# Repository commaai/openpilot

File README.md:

<div align="center" style="text-align: center;">

<h1>openpilot</h1>

<p>
  <b>openpilot is an operating system for robotics.</b>
  <br>
  Currently, it upgrades the driver assistance system in 300+ supported cars.
</p>

<h3>
  <a href="https://docs.comma.ai">Docs</a>
  <span> · </span>
  <a href="https://docs.comma.ai/contributing/roadmap/">Roadmap</a>
  <span> · </span>
  <a href="https://github.com/commaai/openpilot/blob/master/docs/CONTRIBUTING.md">Contribute</a>
  <span> · </span>
  <a href="https://discord.comma.ai">Community</a>
  <span> · </span>
  <a href="https://comma.ai/shop">Try it on a comma four</a>
</h3>

Quick start: `bash <(curl -fsSL openpilot.comma.ai)`

</div>

<table>
  <tr>
    <td></td>
    <td></td>
    <td></td>
  </tr>
</table>

Using openpilot in a car
------

To use openpilot in a car, you need four things:
1. **Supported Device:** a comma four, available at [comma.ai/shop/comma-four](https://www.comma.ai/shop/comma-four).
2. **Software:** The setup procedure for the comma four allows users to enter a URL for custom software. Use the URL `openpilot.comma.ai` to install the release version.
3. **Supported Car:** Ensure that you have one of [the 300+ supported cars](docs/CARS.md).
4. **Car Harness:** You will also need a [car harness](https://comma.ai/shop/car-harness) to connect your comma four to your car.

We have detailed instructions for [how to install the harness and device in a car](https://comma.ai/setup). Note that it's possible to run openpilot on [other hardware](https://blog.comma.ai/self-driving-car-for-free/), although it's not plug-and-play.

### Branches

Running `master` and other branches directly is supported, but it's recommended to run one of the following prebuilt branches:

| comma four branch      | comma 3X branch        | URL                                    | description                                                                         |
|------------------------|------------------------|----------------------------------------|-------------------------------------------------------------------------------------|
| `release-mici`         | `release-tizi`         | openpilot.comma.ai                     | This is openpilot's release branch.                                                 |
| `release-mici-staging` | `release-tizi-staging` | openpilot-test.comma.ai                | This is the staging branch for releases. Use it to get new releases slightly early. |
| `nightly`              | `nightly`              | openpilot-nightly.comma.ai             | This is the bleeding edge development branch. Do not expect this to be stable.      |
| `nightly-dev`          | `nightly-dev`          | installer.comma.ai/commaai/nightly-dev | Same as nightly, but includes experimental development features for some cars.      |

For [chestnut](https://comma.ai/shop/chestnut), use the following installer URLs:

| branch                       | URL                                                        | description                                                                         |
|------------------------------|------------------------------------------------------------|-------------------------------------------------------------------------------------|
| `nightly-chestnut`           | installer.comma.ai/commaai/nightly-chestnut                | This is the bleeding edge development branch. Do not expect this to be stable.      |
| `nightly-chestnut-dev`       | installer.comma.ai/commaai/nightly-chestnut-dev            | Same as nightly, but includes experimental development features for some cars.      |

To start developing openpilot
------

openpilot is developed by [comma](https://comma.ai/) and by users like you. We welcome both pull requests and issues on [GitHub](http://github.com/commaai/openpilot).

* Join the [community Discord](https://discord.comma.ai)
* Check out [the contributing docs](docs/CONTRIBUTING.md)
* Check out the [openpilot tools](openpilot/tools/)
* Code documentation lives at https://docs.comma.ai
* Information about running openpilot lives on the [community wiki](https://github.com/commaai/openpilot/wiki)

Want to get paid to work on openpilot? [comma is hiring](https://comma.ai/jobs#open-positions) and offers lots of [bounties](https://comma.ai/bounties) for external contributors.

Safety and Testing
----

* openpilot observes [ISO26262](https://en.wikipedia.org/wiki/ISO_26262) guidelines, see [SAFETY.md](docs/SAFETY.md) for more details.
* openpilot has software-in-the-loop [tests](.github/workflows/tests.yaml) that run on every commit.
* The code enforcing the safety model lives in panda and is written in C, see [code rigor](https://github.com/commaai/panda#code-rigor) for more details.
* panda has software-in-the-loop [safety tests](https://github.com/commaai/panda/tree/master/tests/safety).
* Internally, we have a hardware-in-the-loop Jenkins test suite that builds and unit tests the various processes.
* panda has additional hardware-in-the-loop [tests](https://github.com/commaai/panda/blob/master/Jenkinsfile).
* We run the latest openpilot in a testing closet containing 10 comma devices continuously replaying routes.

<details>
<summary>MIT Licensed</summary>

openpilot is released under the MIT license. Some parts of the software are released under other licenses as specified.

Any user of this software shall indemnify and hold harmless Comma.ai, Inc. and its directors, officers, employees, agents, stockholders, affiliates, subcontractors and customers from and against all allegations, claims, actions, suits, demands, damages, liabilities, obligations, losses, settlements, judgments, costs and expenses (including without limitation attorneys’ fees and costs) which arise out of, relate to or result from any use of this software by user.

**THIS IS ALPHA QUALITY SOFTWARE FOR RESEARCH PURPOSES ONLY. THIS IS NOT A PRODUCT.
YOU ARE RESPONSIBLE FOR COMPLYING WITH LOCAL LAWS AND REGULATIONS.
NO WARRANTY EXPRESSED OR IMPLIED.**
</details>

<details>
<summary>User Data and comma Account</summary>

By default, openpilot uploads driving data to our servers. You can also access your data through [comma connect](https://connect.comma.ai/). We use your data to train better models and improve openpilot for everyone.

openpilot is open source software, and users can disable data collection if they wish.

openpilot logs the road-facing cameras, CAN, GPS, IMU, magnetometer, thermal sensors, crashes, and operating system logs.
The driver-facing camera and microphone are only logged if you explicitly opt-in in settings.

By using openpilot, you agree to [our Privacy Policy](https://comma.ai/privacy). You understand that use of this software or its related services will generate certain types of user data, which may be logged and stored at the sole discretion of comma. By accepting this agreement, you grant an irrevocable, perpetual, worldwide right to comma for the use of this data.
</details>

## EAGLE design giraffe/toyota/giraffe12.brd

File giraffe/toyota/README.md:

Toyota giraffe
====

Get your panda deeper into your compatible Toyota vehicle

The switches
====

The 4 DIP switches control signals to the stock ADAS system

- 1 -- ADAS CAN1 -> main body CAN

- 2 -- ADAS CAN1 -> panda CAN3 (OBDII pins 12 & 13)

- 3 -- IGNITION POWER -> panda power

- 4 -- ADAS power & ignition -> power & ignition

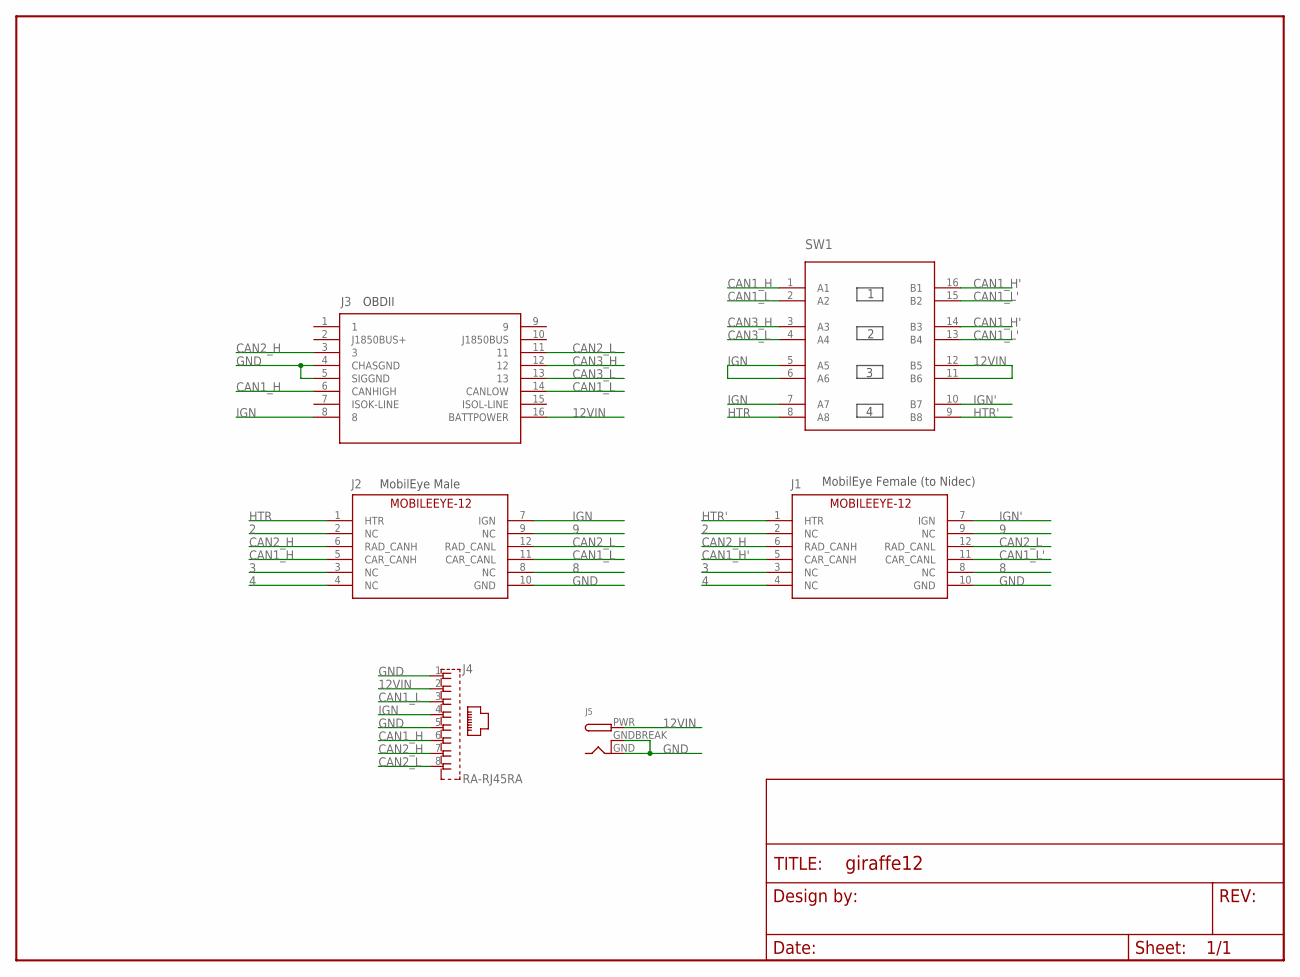
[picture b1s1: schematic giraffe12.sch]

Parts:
FRAME1: FRAME-LETTERNO_PACKAGE; DUMMY
J1: MOBILEEYE-12FEMALE; 2X6-TE-FEMALE
J2: MOBILEEYE-12MALE; 2X6-TE-RA
J3: OBDII-FEMALE-CUT; OBDII-FEMALE-MIDCUT
J4: RA-RJ45RA; RA-RJ45
J5: DCBARRELPTH; DCJACK_2MM_PTH
SW1: 4XDPSTSMT; 4-DPST

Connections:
2: J1.2 (NC), J2.2 (NC)
3: J1.3 (NC), J2.3 (NC)
4: J1.4 (NC), J2.4 (NC)
8: J1.8 (NC), J2.8 (NC)
9: J1.9 (NC), J2.9 (NC)
12VIN: J3.16 (BATTPOWER), J4.2, J5.PWR, SW1.11 (B6), SW1.12 (B5)
CAN1_H: J2.5 (CAR_CANH), J3.6 (CANHIGH), J4.6, SW1.1 (A1)
CAN1_H': J1.5 (CAR_CANH), SW1.14 (B3), SW1.16 (B1)
CAN1_L: J2.11 (CAR_CANL), J3.14 (CANLOW), J4.3, SW1.2 (A2)
CAN1_L': J1.11 (CAR_CANL), SW1.13 (B4), SW1.15 (B2)
CAN2_H: J1.6 (RAD_CANH), J2.6 (RAD_CANH), J3.3, J4.7
CAN2_L: J1.12 (RAD_CANL), J2.12 (RAD_CANL), J3.11, J4.8
CAN3_H: J3.12, SW1.3 (A3)
CAN3_L: J3.13, SW1.4 (A4)
GND: J1.10 (GND), J2.10 (GND), J3.4 (CHASGND), J3.5 (SIGGND), J4.1, J4.5, J5.GND, J5.GNDBREAK
HTR: J2.1 (HTR), SW1.8 (A8)
HTR': J1.1 (HTR), SW1.9 (B8)
IGN: J2.7 (IGN), J3.8, J4.4, SW1.5 (A5), SW1.6 (A6), SW1.7 (A7)
IGN': J1.7 (IGN), SW1.10 (B7)

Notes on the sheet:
OBDII
MobilEye Male
MobilEye Female (to Nidec)

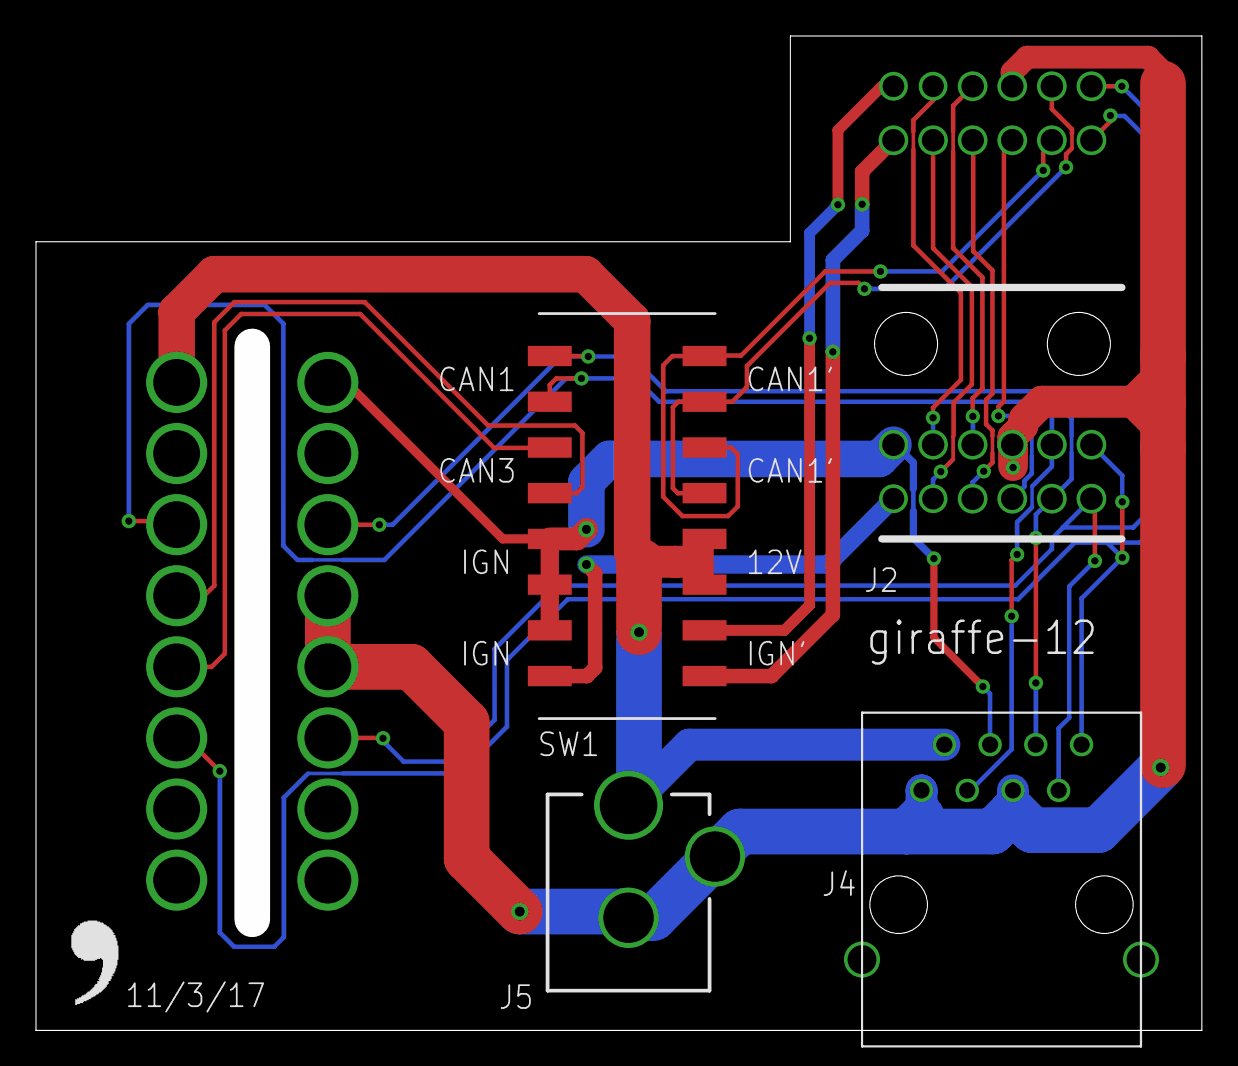
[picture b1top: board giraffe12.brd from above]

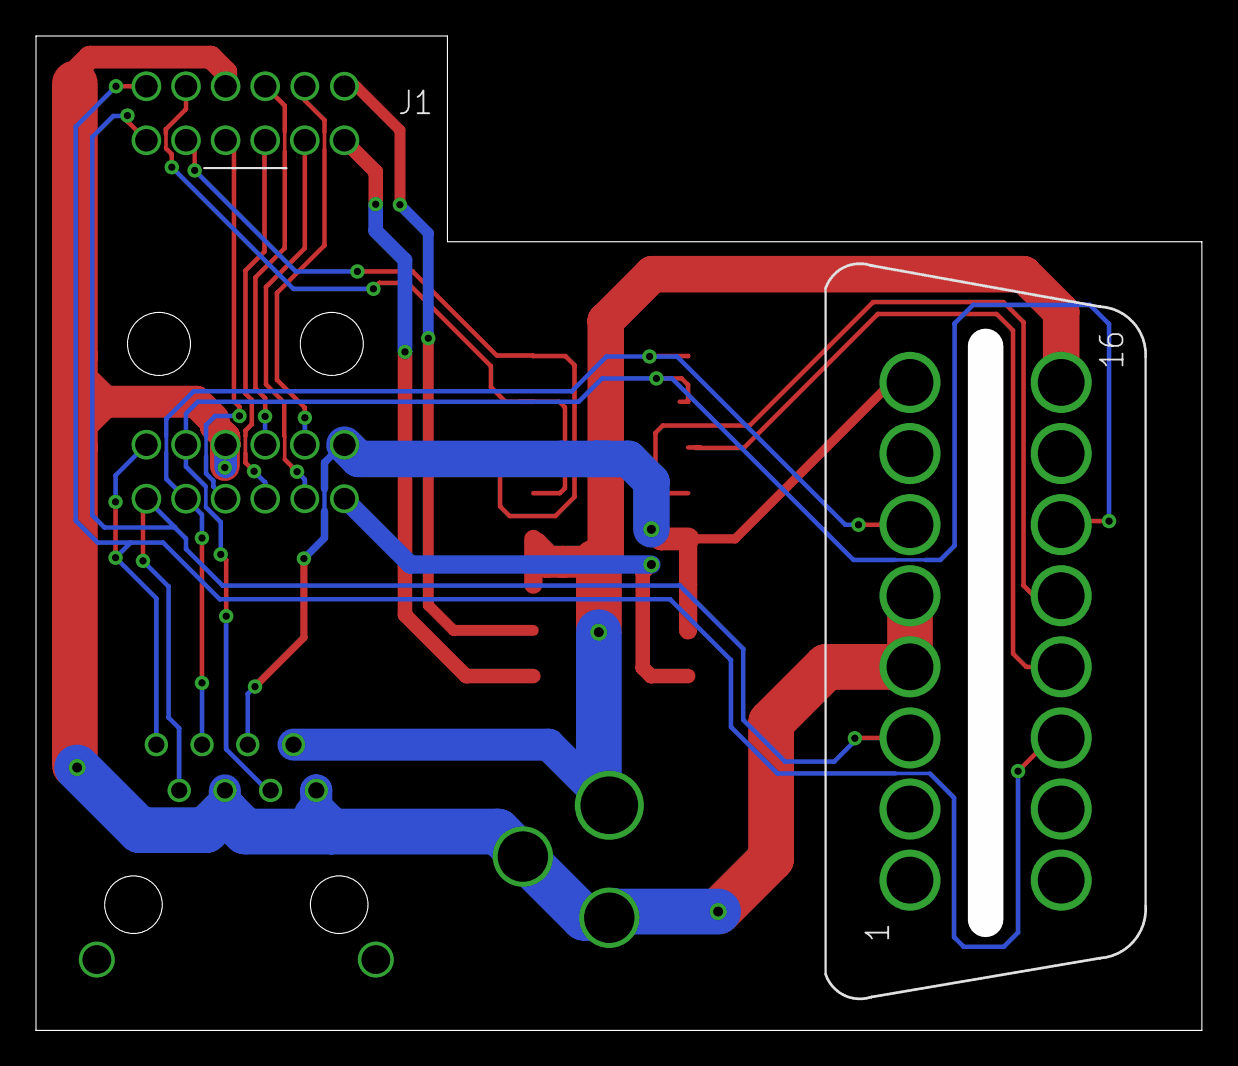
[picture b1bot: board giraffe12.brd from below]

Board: 2 copper layers, 64.8 x 55.2 mm, 8 parts (2 on the bottom side), 19 nets.

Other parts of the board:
U$1: LOGO

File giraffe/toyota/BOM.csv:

Ref Des,Package,Manufacturer PN,Qty,Link
J1,12-pin-RA,1318772-2,1,http://www.mouser.com/Search/ProductDetail.aspx?R=1318772-2v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
J2,12-pin,1318774-1,1,http://www.mouser.com/Search/ProductDetail.aspx?R=1318774-1v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
,,1123343-1,12,https://www.digikey.com/product-detail/en/te-connectivity-am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
,,PRPC040SAAN-RC,1,https://www.digikey.com/products/en?keywords=S1011EC-40-ND
J3,16-pin,OBDII-FEMALE,1,https://cn1514770021qfbj.en.alibaba.com/product/60598699808-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
J4,RJ45-RA,A-2004-2-4-LPS-N-R,1,https://www.digikey.com/product-detail/en/assmann-wsw-compon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
J5,3-pin,EJ508A,1,https://www.digikey.com/products/en?keywords=ej508a
SW1,SMD,204-214ST,1,https://www.digikey.com/scripts/DkSearch/dksus.dll?Detail&it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
SCREWs,Phillips,92010A118,2,https://www.mcmaster.com/#catalog/92010A118

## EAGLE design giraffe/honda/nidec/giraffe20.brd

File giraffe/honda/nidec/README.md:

Honda giraffe
====

Get your panda deeper into your Honda Civic or Acura ILX

The switches
====

The 4 DIP switches control signals to the stock ADAS system

- 1 -- ADAS CAN1 -> main body CAN

- 2 -- ADAS CAN1 -> panda CAN3 (OBDII pins 12 & 13)

- 3 -- ADAS CAN2 -> radar CAN

- 4 -- ADAS power & ignition -> power & ignition

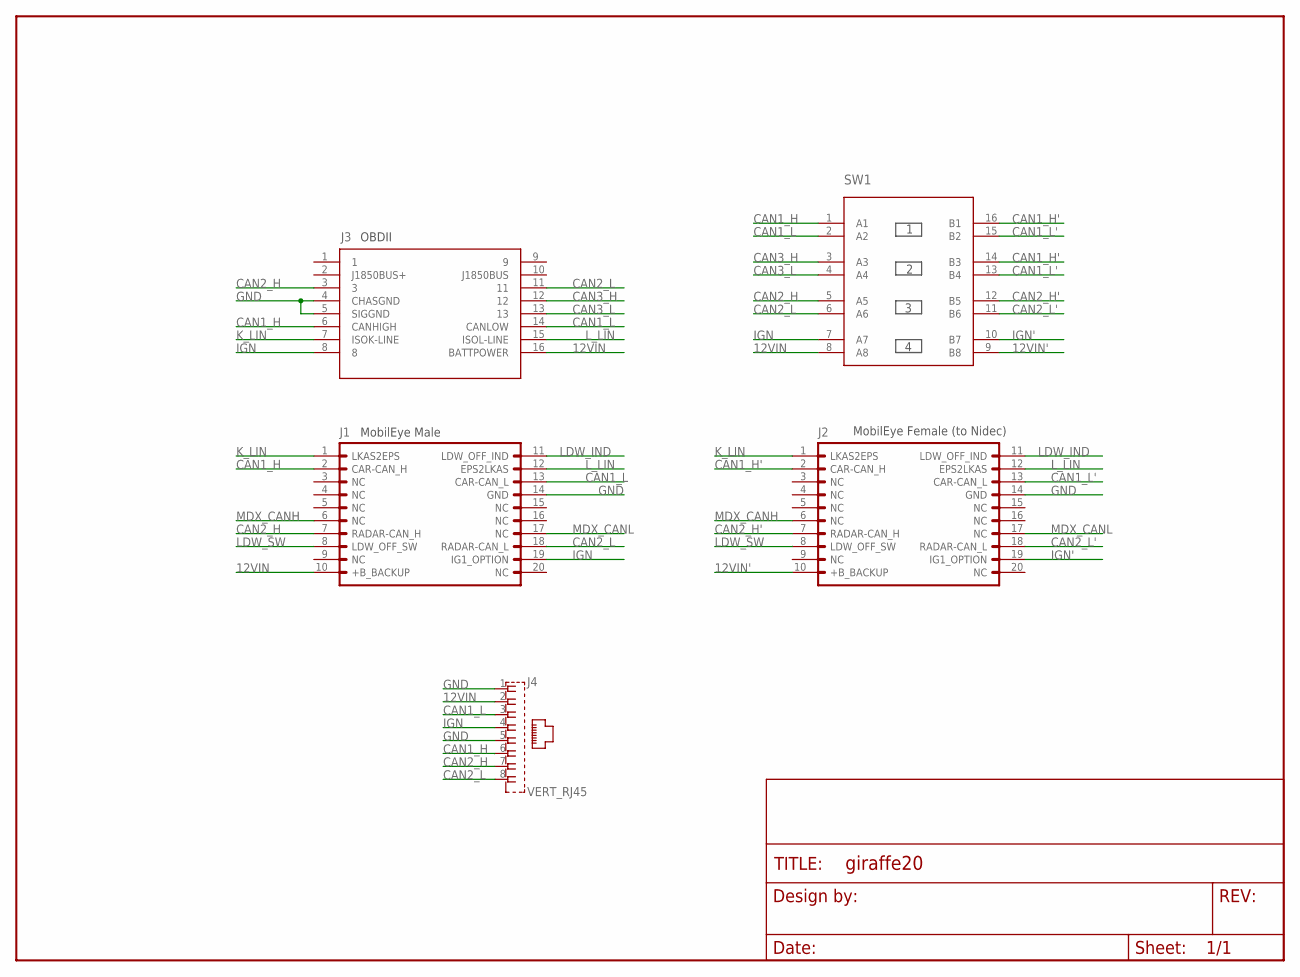
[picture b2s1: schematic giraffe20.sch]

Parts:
FRAME1: FRAME-LETTERNO_PACKAGE; DUMMY
J1: MOBILEYERAMALE; 2X10(RA)
J2: MOBILEYEFEMALE; 2X10(JAE_FEMALE)
J3: OBDII-FEMALE-CUT; OBDII-FEMALE-MIDCUT
J4: VERT_RJ45; GLX-S-88M
SW1: 4XDPSTSMT; 4-DPST

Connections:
12VIN: J1.10 (+B_BACKUP), J3.16 (BATTPOWER), J4.2, SW1.8 (A8)
12VIN': J2.10 (+B_BACKUP), SW1.9 (B8)
CAN1_H: J1.2 (CAR-CAN_H), J3.6 (CANHIGH), J4.6, SW1.1 (A1)
CAN1_H': J2.2 (CAR-CAN_H), SW1.14 (B3), SW1.16 (B1)
CAN1_L: J1.13 (CAR-CAN_L), J3.14 (CANLOW), J4.3, SW1.2 (A2)
CAN1_L': J2.13 (CAR-CAN_L), SW1.13 (B4), SW1.15 (B2)
CAN2_H: J1.7 (RADAR-CAN_H), J3.3, J4.7, SW1.5 (A5)
CAN2_H': J2.7 (RADAR-CAN_H), SW1.12 (B5)
CAN2_L: J1.18 (RADAR-CAN_L), J3.11, J4.8, SW1.6 (A6)
CAN2_L': J2.18 (RADAR-CAN_L), SW1.11 (B6)
CAN3_H: J3.12, SW1.3 (A3)
CAN3_L: J3.13, SW1.4 (A4)
GND: J1.14 (GND), J2.14 (GND), J3.4 (CHASGND), J3.5 (SIGGND), J4.1, J4.5
IGN: J1.19 (IG1_OPTION), J3.8, J4.4, SW1.7 (A7)
IGN': J2.19 (IG1_OPTION), SW1.10 (B7)
K_LIN: J1.1 (LKAS2EPS), J2.1 (LKAS2EPS), J3.7 (ISOK-LINE)
LDW_IND: J1.11 (LDW_OFF_IND), J2.11 (LDW_OFF_IND)
LDW_SW: J1.8 (LDW_OFF_SW), J2.8 (LDW_OFF_SW)
L_LIN: J1.12 (EPS2LKAS), J2.12 (EPS2LKAS), J3.15 (ISOL-LINE)
MDX_CANH: J1.6 (NC), J2.6 (NC)
MDX_CANL: J1.17 (NC), J2.17 (NC)

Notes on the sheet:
OBDII
MobilEye Male
MobilEye Female (to Nidec)

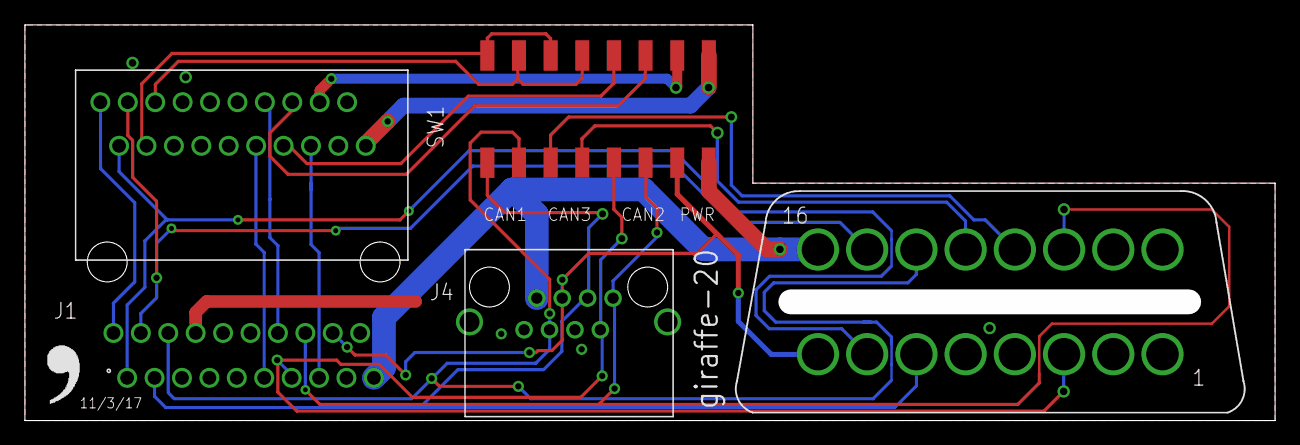
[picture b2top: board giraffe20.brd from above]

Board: 2 copper layers, 100.3 x 31.8 mm, 7 parts (1 on the bottom side), 21 nets.

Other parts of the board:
U$1: LOGO

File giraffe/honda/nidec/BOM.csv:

Ref Des,Package,Manufacturer PN,Qty,Link
J1,20-pin-RA,MX34020NF1,1,https://www.digikey.com/product-detail/en/jae-electronics/MX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
J2,20-pin,MX34020SF1,1,https://www.digikey.com/scripts/DkSearch/dksus.dll?Detail&it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
,,M34S75C4F1,20,https://www.digikey.com/product-detail/en/jae-electronics/M3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
,,PRPC040SAAN-RC,1,https://www.digikey.com/products/en?keywords=S1011EC-40-ND
J3,16-pin,OBDII-FEMALE,1,https://cn1514770021qfbj.en.alibaba.com/product/60598699808-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
J4,RJ45-VERT,A-2014-2-4-LP/FS-R,1,https://www.digikey.com/scripts/DkSearch/dksus.dll?Detail&it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
SW1,SMD,204-214ST,1,https://www.digikey.com/scripts/DkSearch/dksus.dll?Detail&it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
SCREWs,Phillips,92010A118,2,https://www.mcmaster.com/#catalog/92010A118

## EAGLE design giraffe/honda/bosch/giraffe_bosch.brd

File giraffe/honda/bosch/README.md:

Honda giraffe (Bosch ADAS)
====

Get your panda deeper into your:

- 2017+ Honda CR-V
- 2017+ Civic Hatchback
- 2018+ Accord

May fit some Japanese civics or other Hondas with Bosch hardware.

The switches
====

The 4 DIP switches control signals to the stock ADAS system

- 1 -- ADAS CAN1 -> main body CAN

- 2 -- ADAS CAN2 -> camera CAN (OBDII pins 12 & 13)

- 3 -- ADAS CAN2 (from radar) -> panda CAN3

- 4 -- IGN Jumper (jumps IGN to PWR)

Board by [@csouers](https://github.com/csouers) / Case by [@energee](https://github.com/energee)

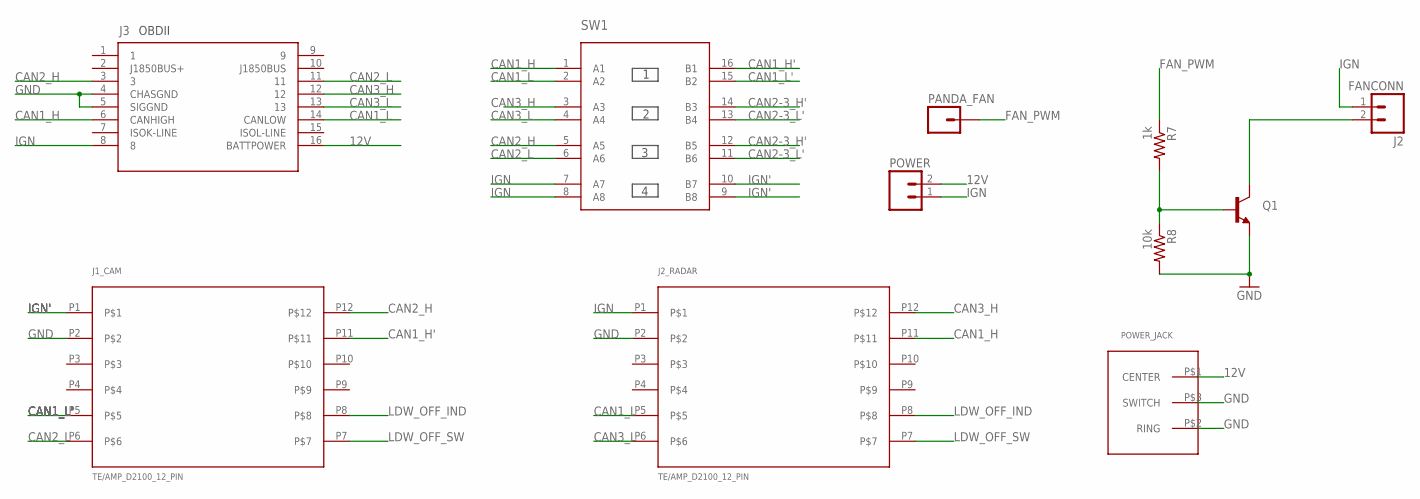
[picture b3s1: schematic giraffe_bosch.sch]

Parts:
J1_CAM, J2_RADAR: TE/AMP_D2100_12_PIN
J2: FANCONN; 1.25CONN
J3: OBDIIFEMALE; OBDII-FEMALE
PANDA_FAN: M01PTH; 1X01
POWER: M02PTH; 1X02
POWER_JACK: PJ-006A-SMT
Q1: MMBT2222A; SOT23-3
R7: 1k; R0603
R8: 10k; R0603
SW1: 4XDPSTSMT; 4-DPST

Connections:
12V: J3.16 (BATTPOWER), POWER.2, POWER_JACK.P$1 (CENTER)
CAN1_H: J2_RADAR.P11, J3.6 (CANHIGH), SW1.1 (A1)
CAN1_H': J1_CAM.P11, SW1.16 (B1)
CAN1_L: J2_RADAR.P5, J3.14 (CANLOW), SW1.2 (A2)
CAN1_L': J1_CAM.P5, SW1.15 (B2)
CAN2-3_H': SW1.12 (B5), SW1.14 (B3)
CAN2-3_L': SW1.11 (B6), SW1.13 (B4)
CAN2_H: J1_CAM.P12, J3.3, SW1.5 (A5)
CAN2_L: J1_CAM.P6, J3.11, SW1.6 (A6)
CAN3_H: J2_RADAR.P12, J3.12, SW1.3 (A3)
CAN3_L: J2_RADAR.P6, J3.13, SW1.4 (A4)
FAN_PWM: PANDA_FAN.1, R7.1
GND: J1_CAM.P2, J2_RADAR.P2, J3.4 (CHASGND), J3.5 (SIGGND), POWER_JACK.P$2 (RING), POWER_JACK.P$3 (SWITCH), Q1.2 (E), R8.2
IGN: J2.1, J2_RADAR.P1, J3.8, POWER.1, SW1.7 (A7), SW1.8 (A8)
IGN': J1_CAM.P1, SW1.9 (B8), SW1.10 (B7)
LDW_OFF_IND: J1_CAM.P8, J2_RADAR.P8
LDW_OFF_SW: J1_CAM.P7, J2_RADAR.P7
unnamed: J2.2, Q1.3 (C)
unnamed: Q1.1 (B), R7.2, R8.1

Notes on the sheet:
OBDII

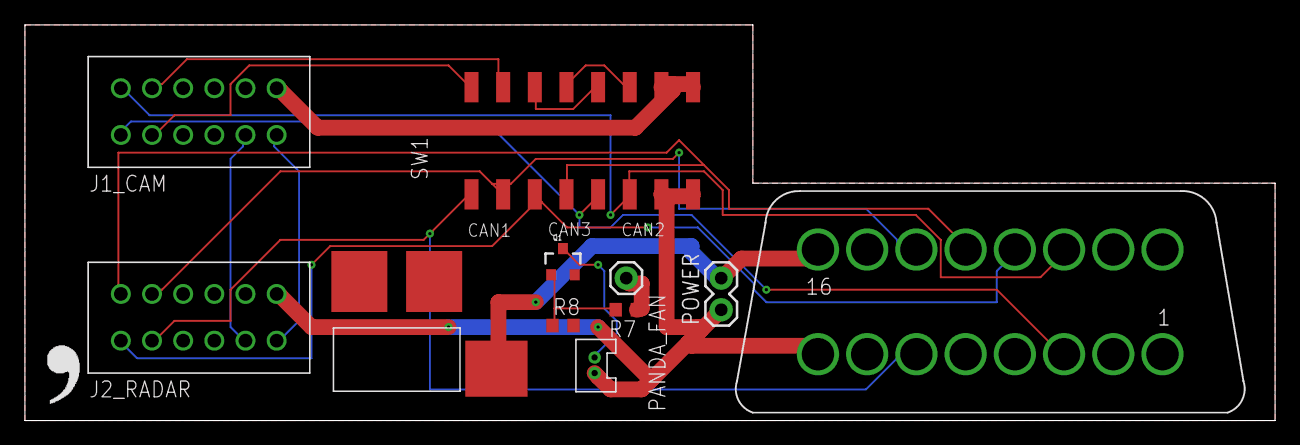
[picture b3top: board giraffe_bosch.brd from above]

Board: 2 copper layers, 100.3 x 31.8 mm, 12 parts (0 on the bottom side), 19 nets.

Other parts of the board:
U$1: LOGO

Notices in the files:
README.md:
License: MIT
parts and their libraries:
SparkFun-DiscreteSemi: Licensing: Creative Commons ShareAlike 4.0 International - https://creativecommons.org/licenses/by-sa/4.0
SparkFun-Aesthetics: Released under the Creative Commons Attribution Share-Alike 4.0 License
SparkFun-Aesthetics: https://creativecommons.org/licenses/by-sa/4.0
